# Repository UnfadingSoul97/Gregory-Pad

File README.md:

# Gregory-Pad
# ⌨️ 
Welcome to my My Gregory PAD a 4x4 macro pad project, designed for the **Hack Club Stardance/Hackpad** mission! it contains an oled display a rotatory encoder with no switch cuz no extra pin and i didnt know about extenstion modules during the time i built this. and it has a neo pixel backdrop.

Link to Project:https://cad.onshape.com/documents/42eb55b7210f8981f69631f1/w/17bebb5454112f4fa155aeb9/e/b8ebbeccbf2a34e7995f6221
---
## 📐 Cad Design

It Has a top cover/Bezel,Switch plate which stays on top of the middle layer so we can sandwich it between the middle body.
The Bottom part is sepaerate so easy access to bottom and led.

---
## 🎮 How to Setup
Solder the diodes to the pcb.
then put some solder into the khalih socket then place the hotswap sockets on it and solder.
Now u can add ur swithes.
Then solder in the PCB,oled display might need some wires soldred to it so it fits in the whole i made.
rotatory knob is good.
now put the switch plate on top and add your switches,Place it on the top of middle body and place the oled in correct postion and place your top cover.
now screw it down with a M2.2mm flat head screw.
the bottom uses M3 screws.
## 🖼️ Image of Gregory

## 🖼️ Image of Schematic

## 🖼️ Image of PCB Design 

## 🖼️ How to fit
   Top Plate can be fitted on top of the switch plate 
   
   First PCB and switch plate are joined together and the switches places and then screwed on to the middle body from the top.(with an m2.2 screw)
   
   The Base,Middle body and top plate are screwed form the bottom with an m.3 screw and it is 19 mm deep.
   
   The switch plate fits inside the the top plate so it looks clean but u can view the top screws from the top.Its to 3d print the same size curves and place then into 
   a arm rest or accessory as per preference.

   Yes I indeed added the steps twice but this one has images so and less details.

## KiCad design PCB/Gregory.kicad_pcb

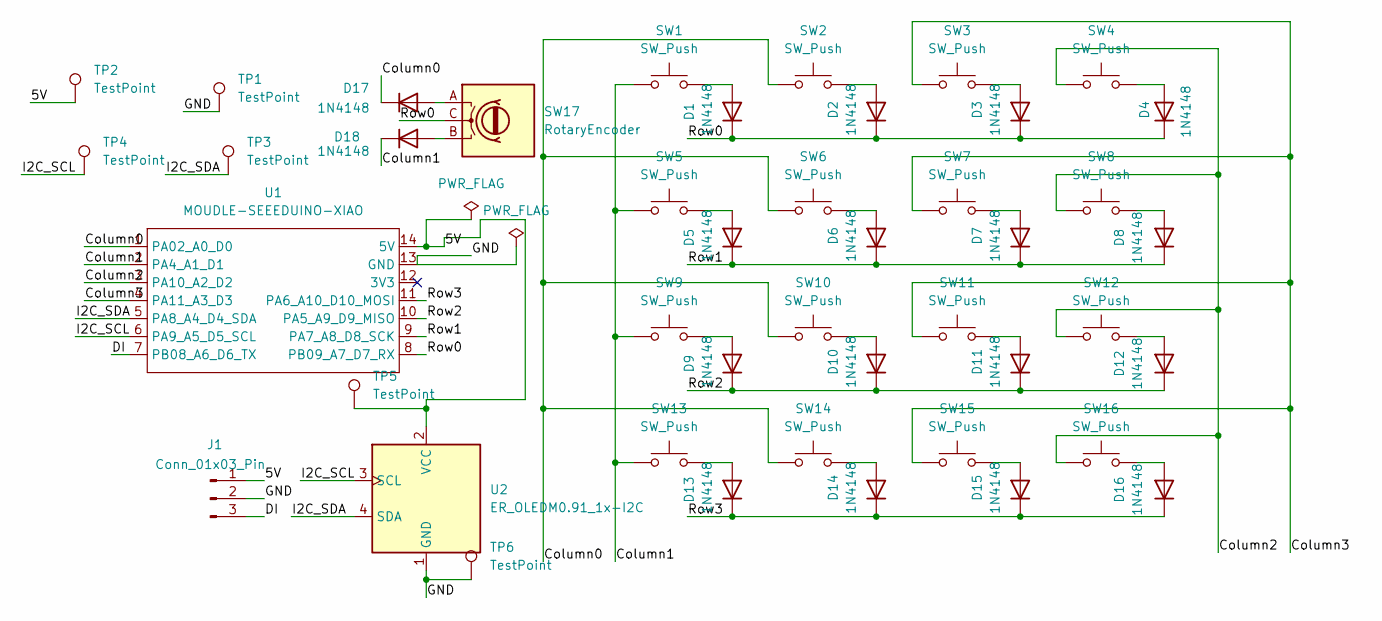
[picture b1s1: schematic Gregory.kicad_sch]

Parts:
D1, D2, D3, D4, D5, D6, D7, D8, D9, D10, D11, D12, D13, D14, D15, D16, D17, D18: 1N4148; D_DO-35_SOD27_P7.62mm_Horizontal
J1: Conn_01x03_Pin; PinHeader_1x03_P2.54mm_Vertical
SW1, SW2, SW3, SW4, SW5, SW6, SW7, SW8, SW9, SW10, SW11, SW12, SW13, SW14, SW15, SW16: SW_Push; MX-Hotswap-1U
SW17: RotaryEncoder; RotaryEncoder_Alps_EC11E_Vertical_H20mm
TP1, TP2, TP3, TP4, TP5, TP6: TestPoint; TestPoint_Pad_D1.5mm
U1: MOUDLE-SEEEDUINO-XIAO; XIAO-Generic-Hybrid-14P-2.54-21X17.8MM
U2: ER_OLEDM0.91_1x-I2C; PinHeader_1x04_P2.54mm_Vertical

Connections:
/5V: J1.1, TP2.1 (1_1), TP5.1 (1_1), U1.14 (5V), U2.2 (VCC)
/Column0: D17.1 (K), SW2.1, SW6.1, SW10.1, SW14.1, U1.1 (PA02_A0_D0)
/Column1: D18.1 (K), SW1.1, SW5.1, SW9.1, SW13.1, U1.2 (PA4_A1_D1)
/Column2: SW4.1, SW8.1, SW12.1, SW16.1, U1.3 (PA10_A2_D2)
/Column3: SW3.1, SW7.1, SW11.1, SW15.1, U1.4 (PA11_A3_D3)
/DI: J1.3, U1.7 (PB08_A6_D6_TX)
/GND: J1.2, TP1.1 (1_1), TP6.1 (1_1), U1.13 (GND), U2.1 (GND)
/I2C_SCL: TP4.1 (1_1), U1.6 (PA9_A5_D5_SCL), U2.3 (SCL)
/I2C_SDA: TP3.1 (1_1), U1.5 (PA8_A4_D4_SDA), U2.4 (SDA)
/Row0: D1.1 (K), D2.1 (K), D3.1 (K), D4.1 (K), SW17.C, U1.8 (PB09_A7_D7_RX)
/Row1: D5.1 (K), D6.1 (K), D7.1 (K), D8.1 (K), U1.9 (PA7_A8_D8_SCK)
/Row2: D9.1 (K), D10.1 (K), D11.1 (K), D12.1 (K), U1.10 (PA5_A9_D9_MISO)
/Row3: D13.1 (K), D14.1 (K), D15.1 (K), D16.1 (K), U1.11 (PA6_A10_D10_MOSI)
unnamed: D1.2 (A), SW1.2
unnamed: D2.2 (A), SW2.2
unnamed: D3.2 (A), SW3.2
unnamed: D4.2 (A), SW4.2
unnamed: D5.2 (A), SW5.2
unnamed: D6.2 (A), SW6.2
unnamed: D7.2 (A), SW7.2
unnamed: D8.2 (A), SW8.2
unnamed: D9.2 (A), SW9.2
unnamed: D10.2 (A), SW10.2
unnamed: D11.2 (A), SW11.2
unnamed: D12.2 (A), SW12.2
unnamed: D13.2 (A), SW13.2
unnamed: D14.2 (A), SW14.2
unnamed: D15.2 (A), SW15.2
unnamed: D16.2 (A), SW16.2
unnamed: D17.2 (A), SW17.A
unnamed: D18.2 (A), SW17.B

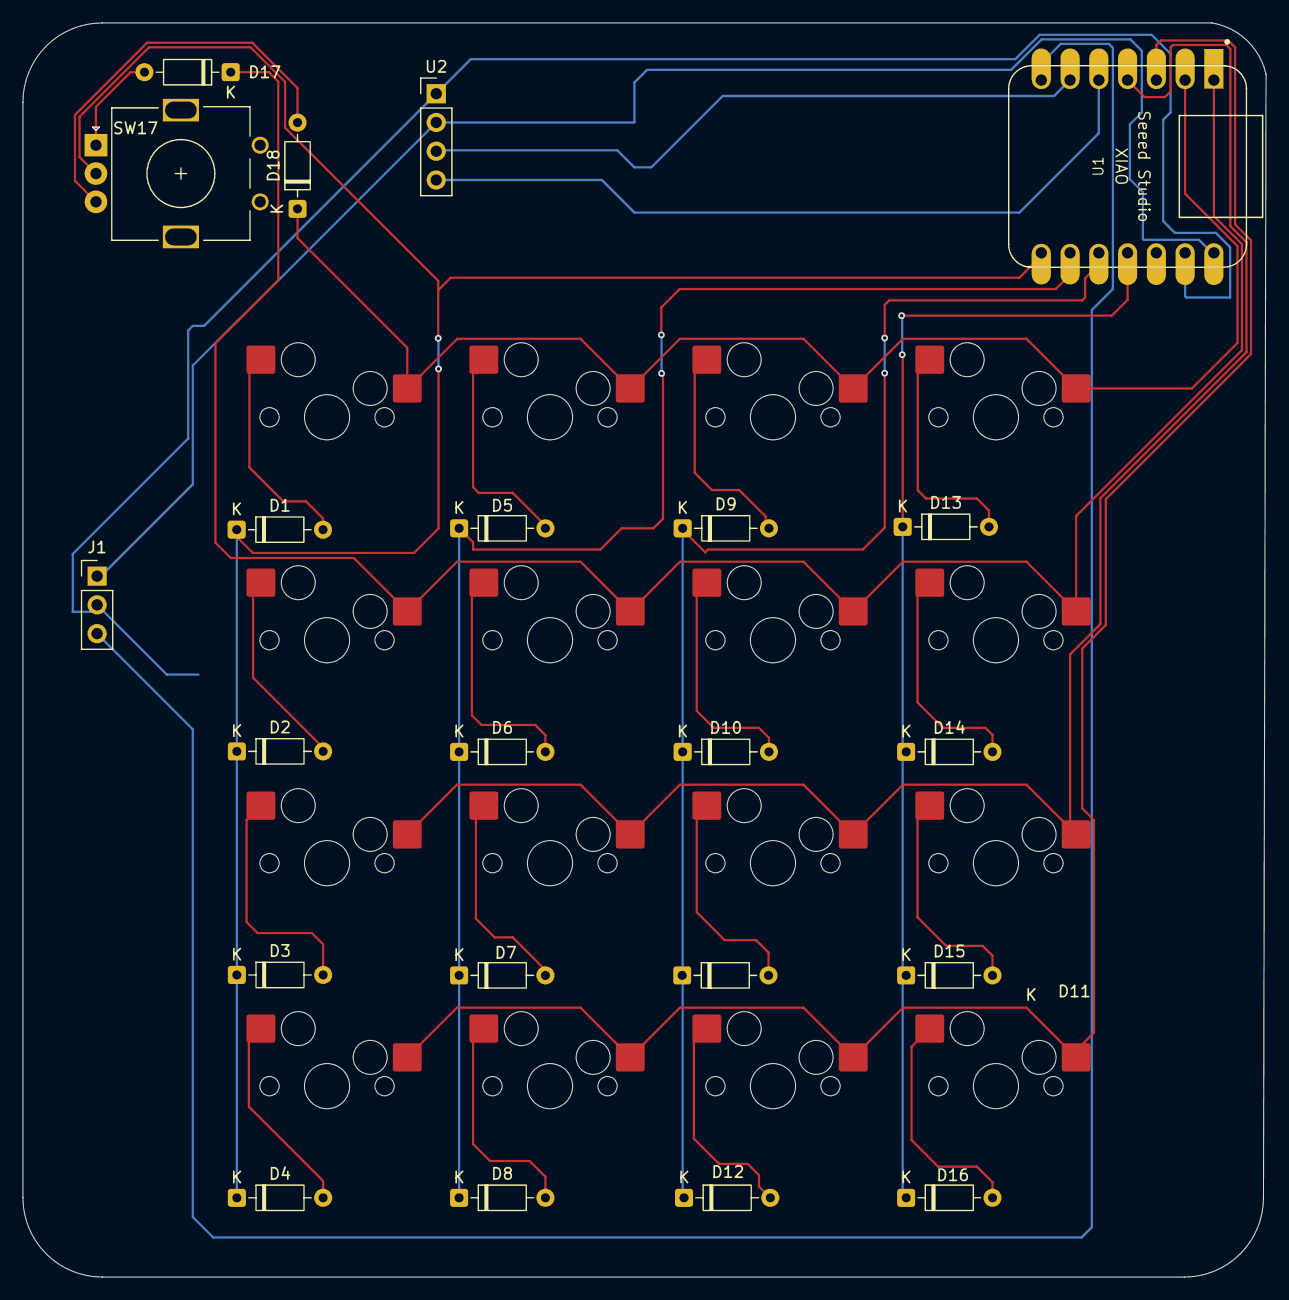
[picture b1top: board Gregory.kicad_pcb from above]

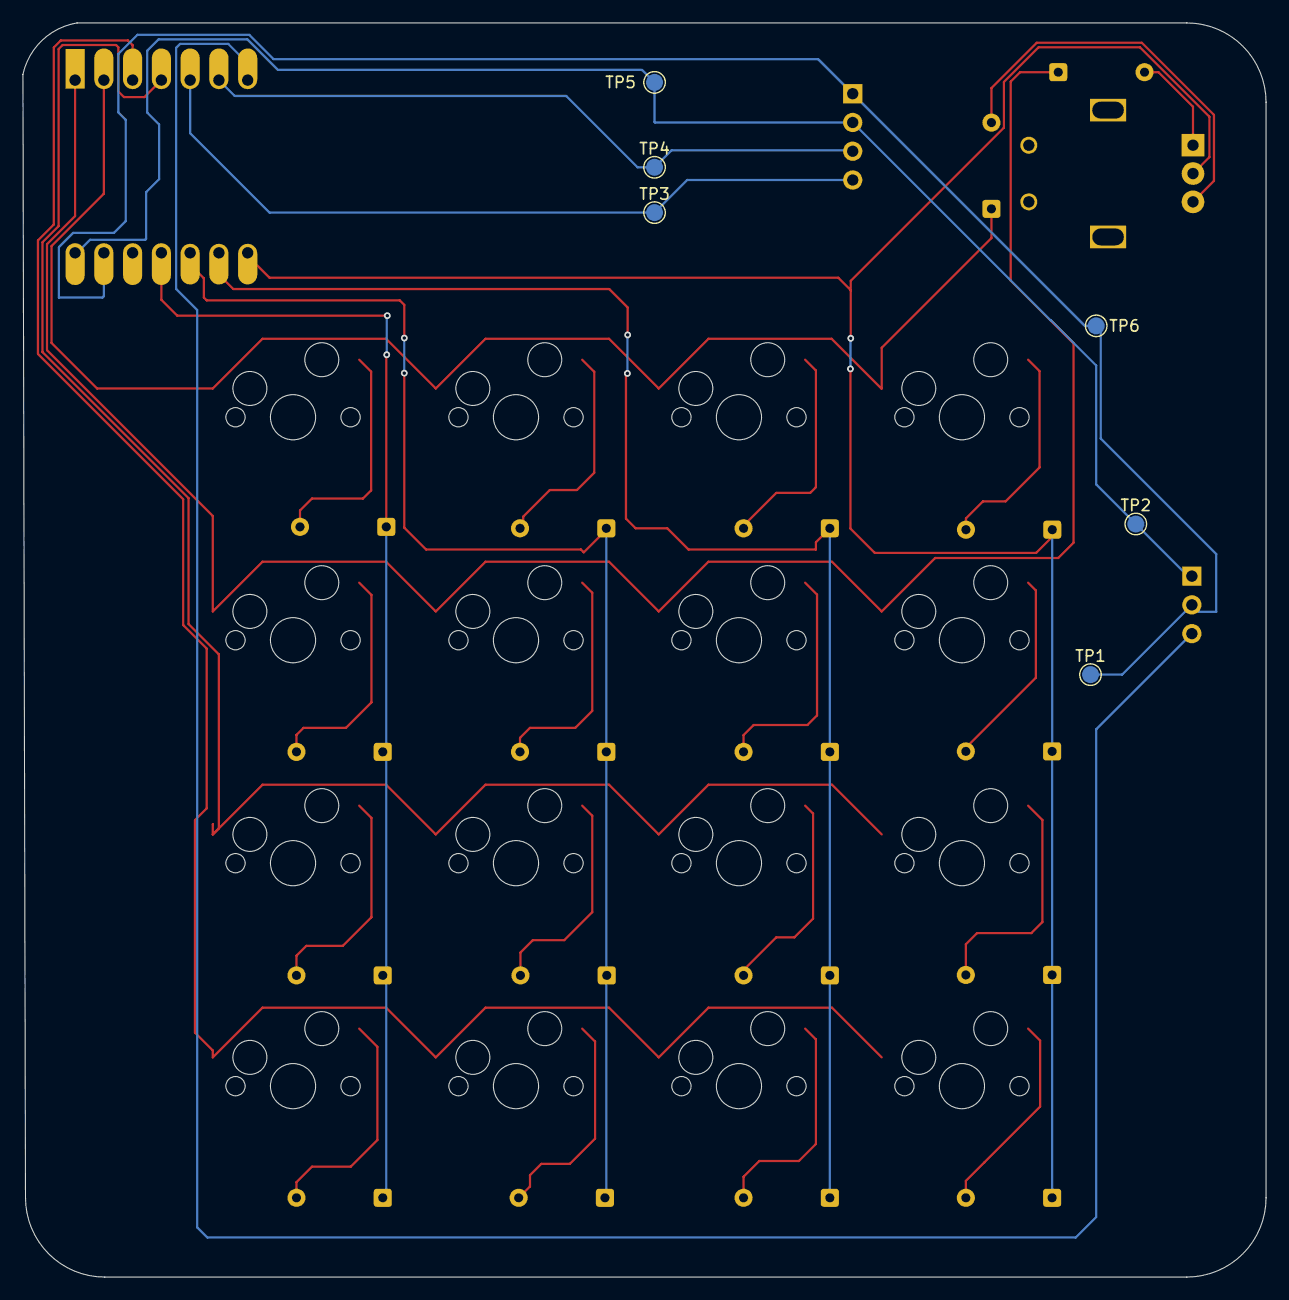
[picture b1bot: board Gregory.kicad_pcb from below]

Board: 2 copper layers, 109.8 x 110.8 mm, 44 parts (6 on the bottom side), 31 nets.

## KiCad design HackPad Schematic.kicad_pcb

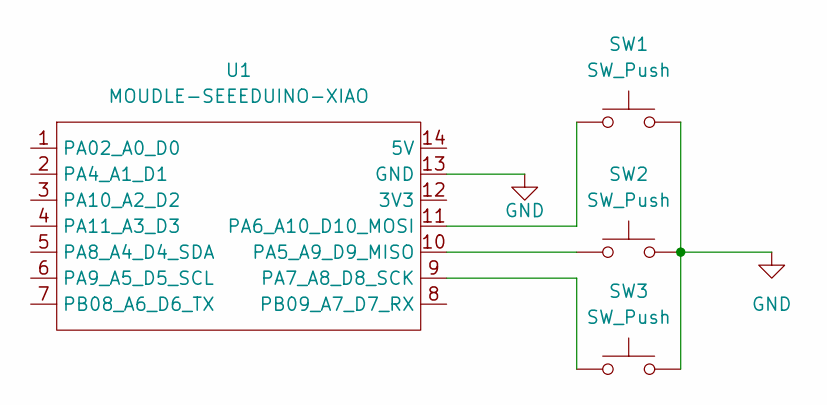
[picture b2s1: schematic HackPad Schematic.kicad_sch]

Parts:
SW1, SW2, SW3: SW_Push; SW_Cherry_MX_1.00u_PCB
U1: MOUDLE-SEEEDUINO-XIAO; XIAO-Generic-Hybrid-14P-2.54-21X17.8MM

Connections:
GND: SW1.2, SW2.2, SW3.2, U1.13 (GND)
unnamed: SW2.1, U1.10 (PA5_A9_D9_MISO)
unnamed: SW1.1, U1.11 (PA6_A10_D10_MOSI)
unnamed: SW3.1, U1.9 (PA7_A8_D8_SCK)

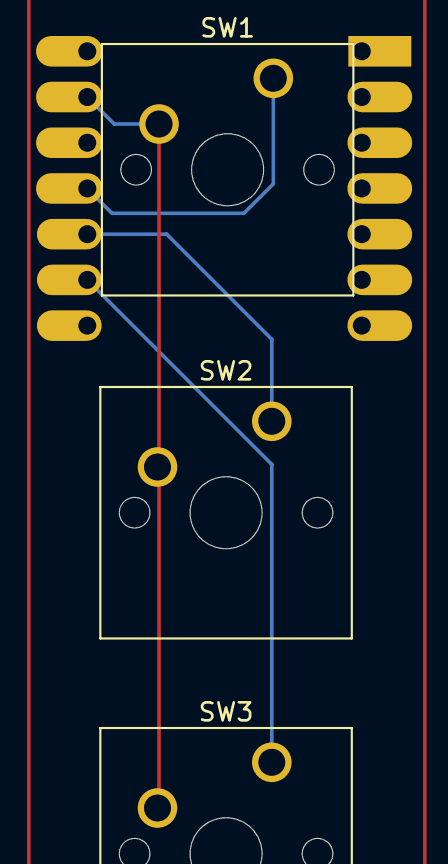
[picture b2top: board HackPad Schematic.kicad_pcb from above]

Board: 2 copper layers, 4 parts (1 on the bottom side), 4 nets.
